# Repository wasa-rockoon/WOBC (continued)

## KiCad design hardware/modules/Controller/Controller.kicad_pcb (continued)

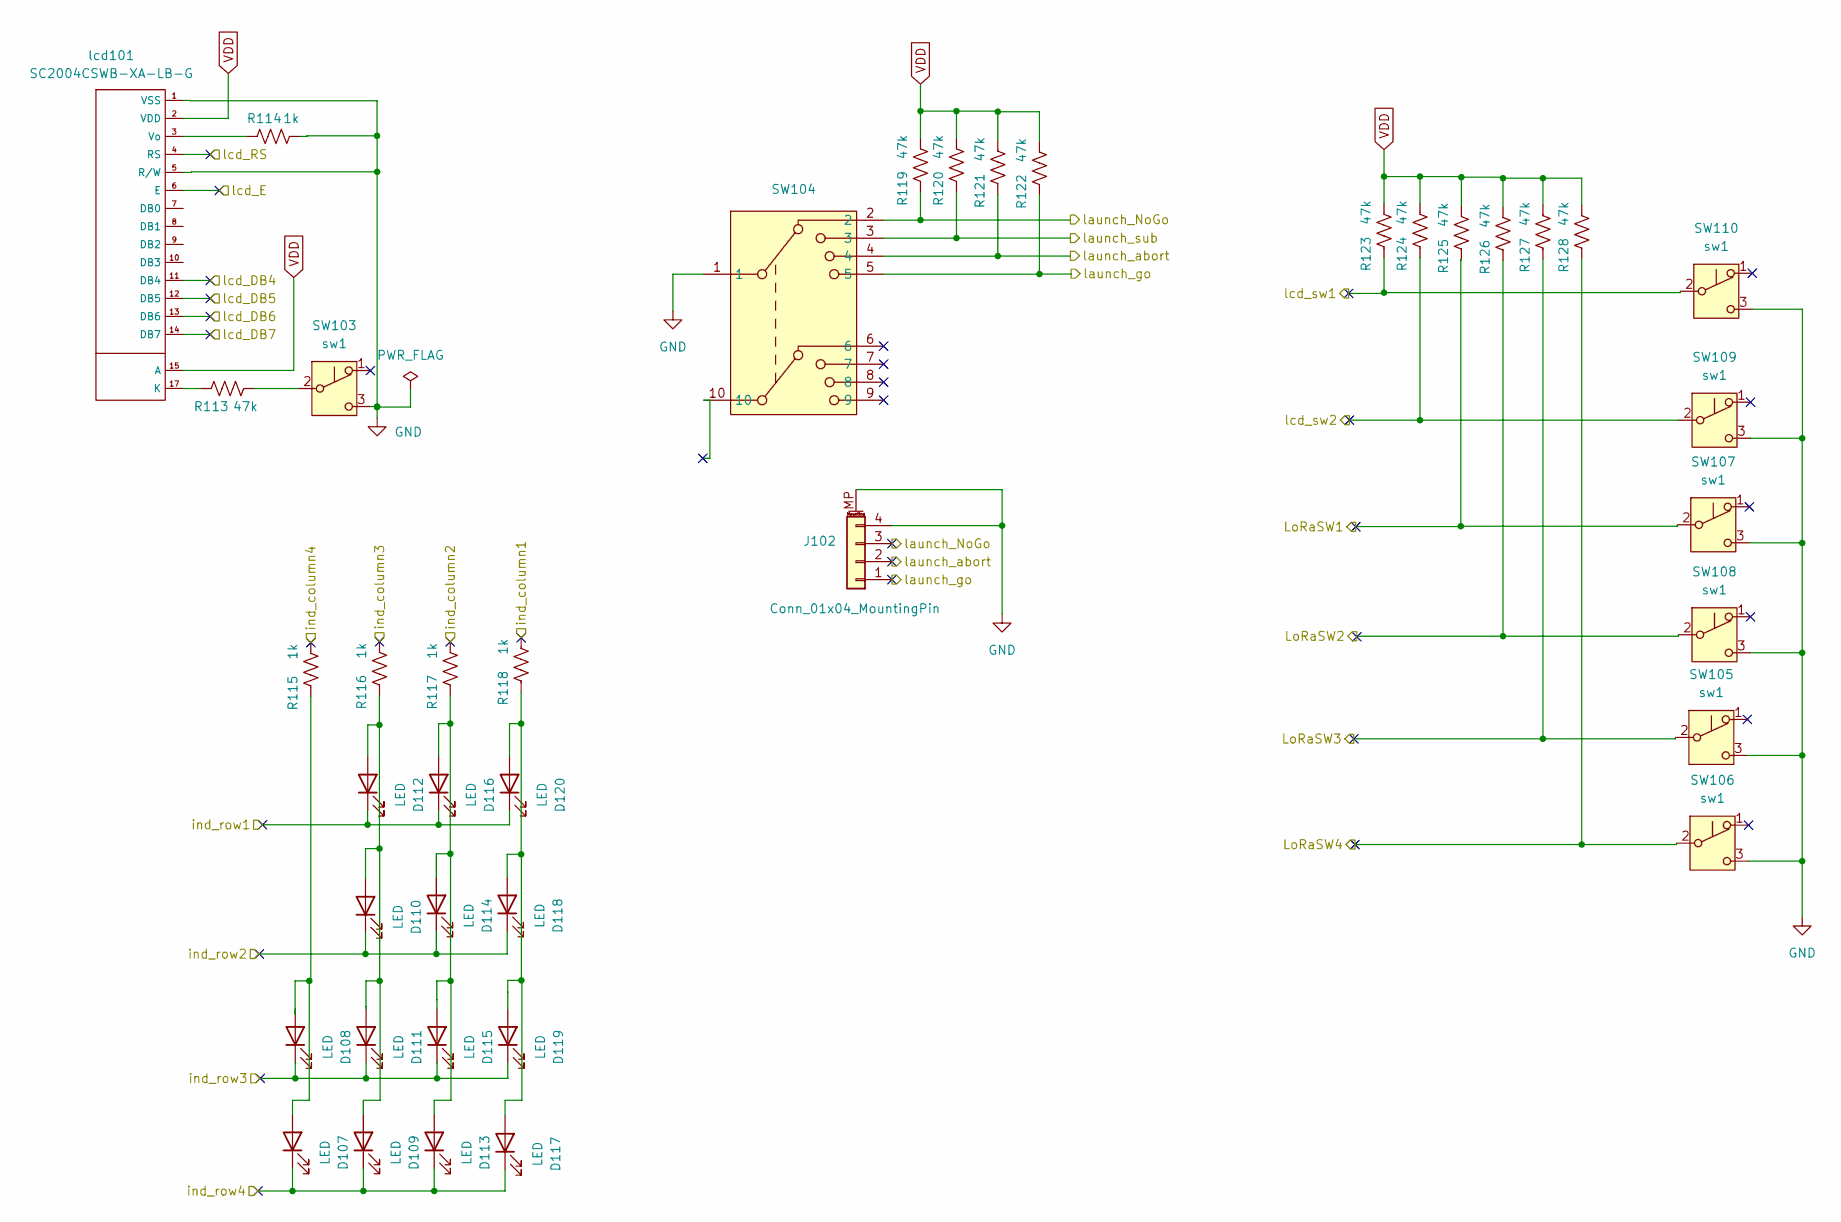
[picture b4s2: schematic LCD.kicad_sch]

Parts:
D107, D108, D109, D110, D111, D112, D113, D114, D115, D116, D117, D118, D119, D120: LED; LED_D3.0mm_FlatTop
J102: Conn_01x04_MountingPin; Grove_4P_L_SMD
R113, R119, R120, R121, R122, R123, R124, R125, R126, R127, R128: 47k; C_0402_1005Metric; LCSC C25792
R114, R115, R116, R117, R118: 1k; C_0402_1005Metric; LCSC C11702
SW103, SW105, SW106, SW107, SW108, SW109, SW110: sw1; ToggleSwitch
SW104: RotarySwitch_2x04
lcd101: SC2004CSWB-XA-LB-G; SC2004CSWB

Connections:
/DB4: lcd101.11 (DB4); also elsewhere on the board
/DB5: lcd101.12 (DB5); also elsewhere on the board
/DB6: lcd101.13 (DB6); also elsewhere on the board
/DB7: lcd101.14 (DB7); also elsewhere on the board
/E: lcd101.6 (E); also elsewhere on the board
/Go: J102.1, R122.2, SW104.5; also elsewhere on the board
/LoRa1sw: R125.2, SW107.2 (B); also elsewhere on the board
/LoRa2sw: R126.2, SW108.2 (B); also elsewhere on the board
/LoRa3sw: R127.2, SW105.2 (B); also elsewhere on the board
/LoRa4sw: R128.2, SW106.2 (B); also elsewhere on the board
/NoGo: J102.3, R119.2, SW104.2; also elsewhere on the board
/RS: lcd101.4 (RS); also elsewhere on the board
/abort: J102.2, R121.2, SW104.4; also elsewhere on the board
/col1: R118.1; also elsewhere on the board
/col2: R117.1; also elsewhere on the board
/col3: R116.1; also elsewhere on the board
/col4: R115.1; also elsewhere on the board
/lcd_sw1: R123.2, SW110.2 (B); also elsewhere on the board
/lcd_sw2: R124.2, SW109.2 (B); also elsewhere on the board
/raw1: D112.1 (K), D116.1 (K), D120.1 (K); also elsewhere on the board
/raw2: D110.1 (K), D114.1 (K), D118.1 (K); also elsewhere on the board
/raw3: D108.1 (K), D111.1 (K), D115.1 (K), D119.1 (K); also elsewhere on the board
/raw4: D107.1 (K), D109.1 (K), D113.1 (K), D117.1 (K); also elsewhere on the board
/sub: R120.2, SW104.3; also elsewhere on the board
GND: J102.4, J102.MP (MountPin), R114.1, SW103.3 (C), SW104.1, SW105.3 (C), SW106.3 (C), SW107.3 (C), SW108.3 (C), SW109.3 (C), SW110.3 (C), lcd101.1 (VSS), lcd101.5 (R/W); also elsewhere on the board
unnamed: D107.2 (A), D108.2 (A), R115.2
unnamed: D109.2 (A), D110.2 (A), D111.2 (A), D112.2 (A), R116.2
unnamed: D113.2 (A), D114.2 (A), D115.2 (A), D116.2 (A), R117.2
unnamed: D117.2 (A), D118.2 (A), D119.2 (A), D120.2 (A), R118.2
unnamed: R113.1, SW103.2 (B)
unnamed: R113.2, lcd101.17 (K)
unnamed: R114.2, lcd101.3 (Vo)
VDD: R119.1, R120.1, R121.1, R122.1, R123.1, R124.1, R125.1, R126.1, R127.1, R128.1, lcd101.2 (VDD), lcd101.15 (A); also elsewhere on the board

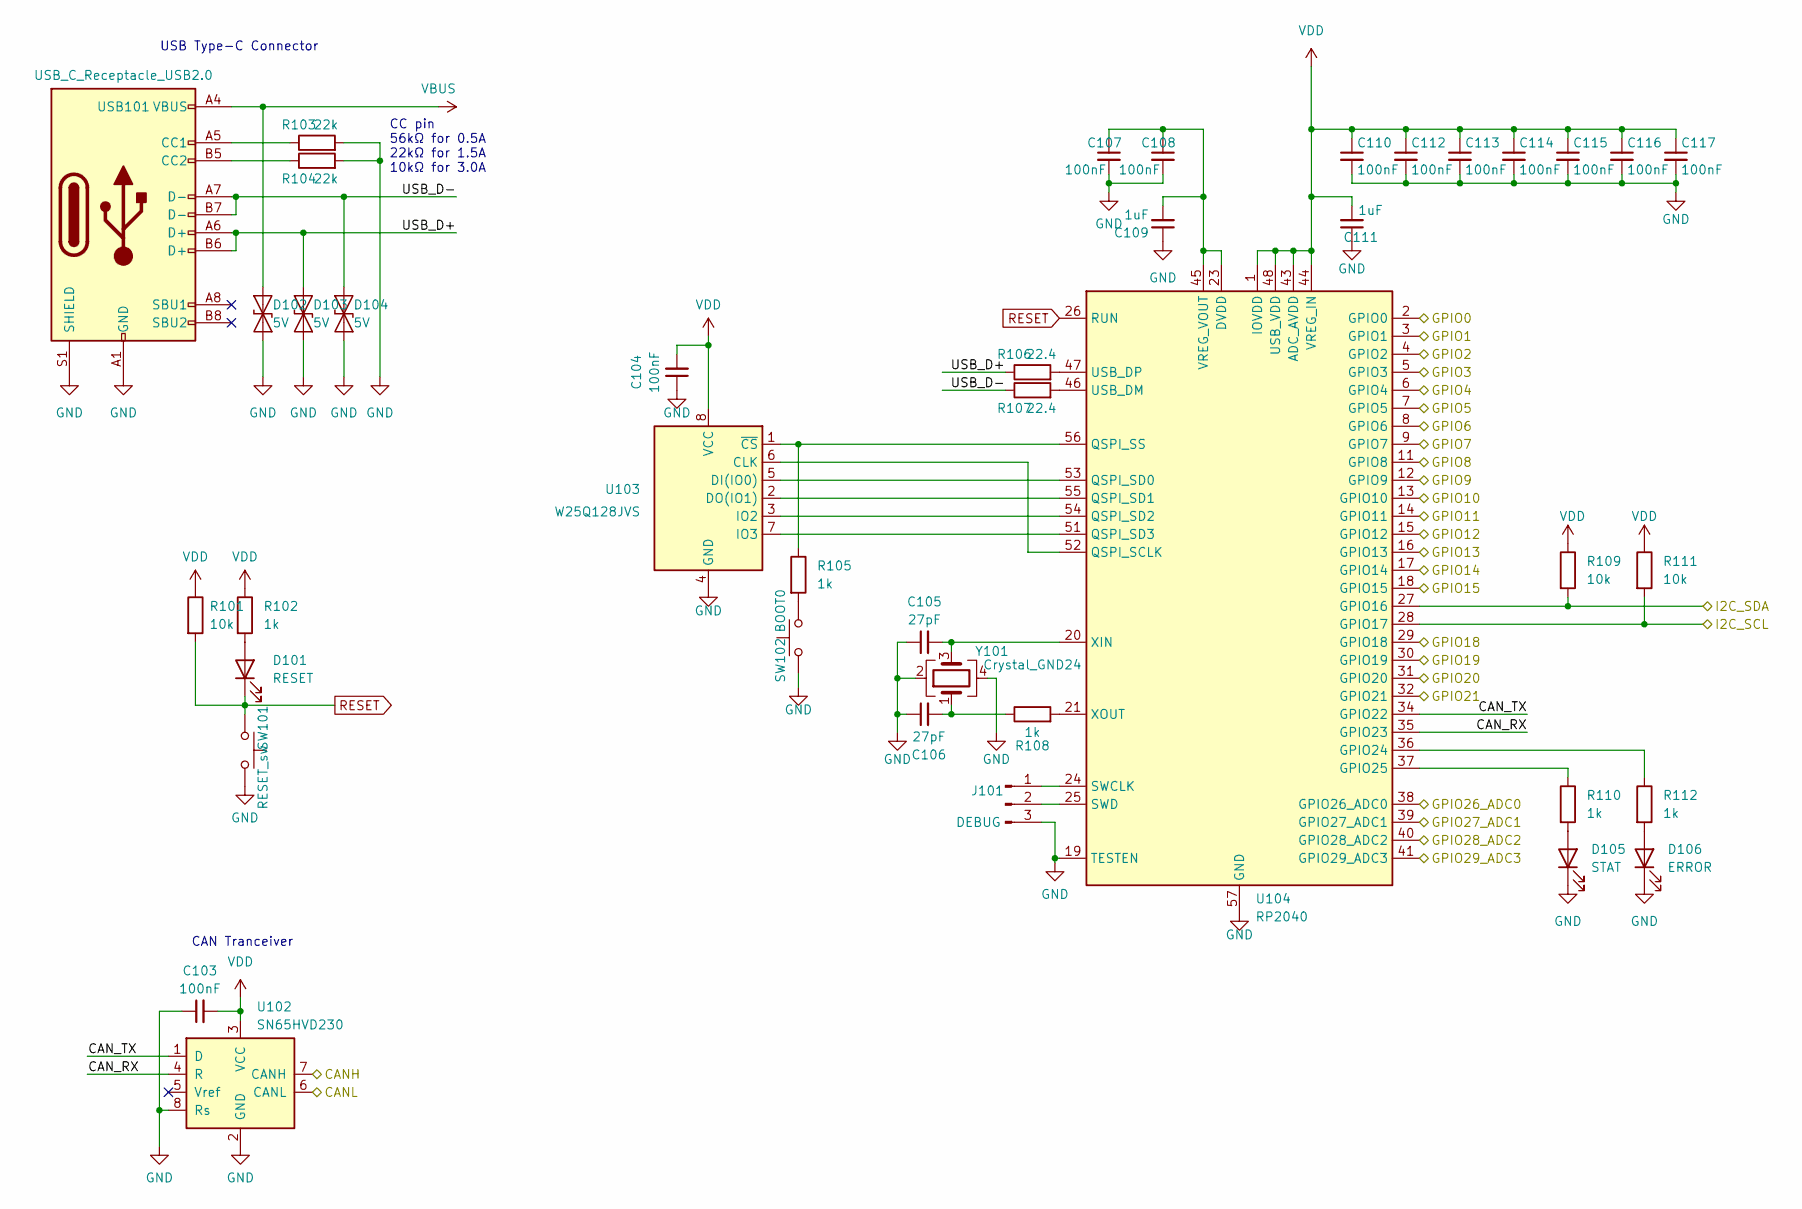
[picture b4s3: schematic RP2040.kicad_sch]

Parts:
C103, C104, C107, C108, C110, C112, C113, C114, C115, C116, C117: 100nF; C_0402_1005Metric; LCSC C1525
C105, C106: 27pF; C_0402_1005Metric; LCSC C1555
C109, C111: 1uF; C_0402_1005Metric; LCSC C52923
D101: RESET; LED_0805_2012Metric; LCSC C2296
D102, D103, D104: 5V; D_SOD-882; LCSC C7420372
D105: STAT; LED_0805_2012Metric; LCSC C2297
D106: ERROR; LED_0805_2012Metric; LCSC C84256
J101: DEBUG; PinHeader_1x03_P1.27mm_Vertical
R101, R109, R111: 10k; R_0402_1005Metric; LCSC C25744
R102, R105, R108, R110, R112: 1k; R_0402_1005Metric; LCSC C11702
R103, R104: 22k; R_0402_1005Metric; LCSC C25768
R106, R107: 22.4; R_0402_1005Metric; LCSC C25092
SW101: RESET_sw; TVAF06-A020B-R
SW102: BOOT0; TVAF06-A020B-R
U102: SN65HVD230; SOIC-8_3.9x4.9mm_P1.27mm; LCSC C12084
U103: W25Q128JVS; SOIC-8_5.23x5.23mm_P1.27mm; LCSC C97521
U104: RP2040; QFN-56-1EP_7x7mm_P0.4mm_EP3.2x3.2mm; LCSC C2040
USB101: USB_C_Receptacle_USB2.0; USB_C_TYPEC-301S-ACP16X7; LCSC C2856766
Y101: Crystal_GND24; Crystal_SMD_3225-4Pin_3.2x2.5mm; LCSC C9002

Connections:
/DB4: U104.11 (GPIO8); also elsewhere on the board
/DB5: U104.12 (GPIO9); also elsewhere on the board
/DB6: U104.13 (GPIO10); also elsewhere on the board
/DB7: U104.14 (GPIO11); also elsewhere on the board
/E: U104.9 (GPIO7); also elsewhere on the board
/Go: U104.5 (GPIO3); also elsewhere on the board
/LoRa1sw: U104.18 (GPIO15); also elsewhere on the board
/LoRa2sw: U104.17 (GPIO14); also elsewhere on the board
/LoRa3sw: U104.16 (GPIO13); also elsewhere on the board
/LoRa4sw: U104.15 (GPIO12); also elsewhere on the board
/ModuleIF/CANH: U102.7 (CANH); also elsewhere on the board
/ModuleIF/CANL: U102.6 (CANL); also elsewhere on the board
/NoGo: U104.2 (GPIO0); also elsewhere on the board
/RP2040/CAN_RX: U102.4 (R), U104.35 (GPIO23)
/RP2040/CAN_TX: U102.1 (D), U104.34 (GPIO22)
/RP2040/I2C_SCL: R111.2, U104.28 (GPIO17)
/RP2040/I2C_SDA: R109.2, U104.27 (GPIO16)
/RP2040/USB_D+: D103.2 (A2), R106.1, USB101.A6 (D+), USB101.B6 (D+)
/RP2040/USB_D-: D104.2 (A2), R107.1, USB101.A7 (D-), USB101.B7 (D-)
/RS: U104.6 (GPIO4); also elsewhere on the board
/abort: U104.4 (GPIO2); also elsewhere on the board
/col1: U104.38 (GPIO26_ADC0); also elsewhere on the board
/col2: U104.39 (GPIO27_ADC1); also elsewhere on the board
/col3: U104.40 (GPIO28_ADC2); also elsewhere on the board
/col4: U104.41 (GPIO29_ADC3); also elsewhere on the board
/lcd_sw1: U104.32 (GPIO21); also elsewhere on the board
/lcd_sw2: U104.31 (GPIO20); also elsewhere on the board
/raw1: U104.7 (GPIO5); also elsewhere on the board
/raw2: U104.8 (GPIO6); also elsewhere on the board
/raw3: U104.29 (GPIO18); also elsewhere on the board
/raw4: U104.30 (GPIO19); also elsewhere on the board
/sub: U104.3 (GPIO1); also elsewhere on the board
GND: C103.1, C104.1, C105.1, C106.1, C107.2, C108.2, C109.1, C110.2, C111.1, C112.2, C113.2, C114.2, C115.2, C116.2, C117.2, D102.1 (A1), D103.1 (A1), D104.1 (A1), D105.1 (K), D106.1 (K), J101.3, R103.2, R104.2, SW101.2, SW102.1, U102.2 (GND), U102.8 (Rs), U103.4 (GND), U104.19 (TESTEN), U104.57 (GND), USB101.A1 (GND), USB101.A12 (GND), USB101.B1 (GND), USB101.B12 (GND), USB101.S1 (SHIELD), Y101.2, Y101.4; also elsewhere on the board
unnamed: C106.2, R108.1, Y101.1
unnamed: D101.2 (A), R102.2
unnamed: D105.2 (A), R110.2
unnamed: D106.2 (A), R112.2
unnamed: J101.1, U104.24 (SWCLK)
unnamed: J101.2, U104.25 (SWD)
unnamed: R105.2, SW102.2
unnamed: U103.6 (CLK), U104.52 (QSPI_SCLK)
unnamed: U103.5 (DI(IO0)), U104.53 (QSPI_SD0)
unnamed: U103.2 (DO(IO1)), U104.55 (QSPI_SD1)
unnamed: U103.3 (IO2), U104.54 (QSPI_SD2)
unnamed: U103.7 (IO3), U104.51 (QSPI_SD3)
unnamed: R105.1, U103.1 (~CS), U104.56 (QSPI_SS)
unnamed: R112.1, U104.36 (GPIO24)
unnamed: R110.1, U104.37 (GPIO25)
unnamed: R107.2, U104.46 (USB_DM)
unnamed: R106.2, U104.47 (USB_DP)
unnamed: C107.1, C108.1, C109.2, U104.23 (DVDD), U104.45 (VREG_VOUT), U104.50 (DVDD)
unnamed: C105.2, U104.20 (XIN), Y101.3
unnamed: R108.2, U104.21 (XOUT)
unnamed: R103.1, USB101.A5 (CC1)
unnamed: R104.1, USB101.B5 (CC2)
RESET: D101.1 (K), R101.2, SW101.1, U104.26 (RUN)
VBUS: D102.2 (A2), USB101.A4 (VBUS), USB101.A9 (VBUS), USB101.B4 (VBUS), USB101.B9 (VBUS); also elsewhere on the board
VDD: C103.2, C104.2, C110.1, C111.2, C112.1, C113.1, C114.1, C115.1, C116.1, C117.1, R101.1, R102.1, R109.1, R111.1, U102.3 (VCC), U103.8 (VCC), U104.1 (IOVDD), U104.10 (IOVDD), U104.22 (IOVDD), U104.33 (IOVDD), U104.42 (IOVDD), U104.43 (ADC_AVDD), U104.44 (VREG_IN), U104.48 (USB_VDD), U104.49 (IOVDD); also elsewhere on the board

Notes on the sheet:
CAN Tranceiver
USB Type-C Connector
CC pin 56kΩ for 0.5A 22kΩ for 1.5A 10kΩ for 3.0A

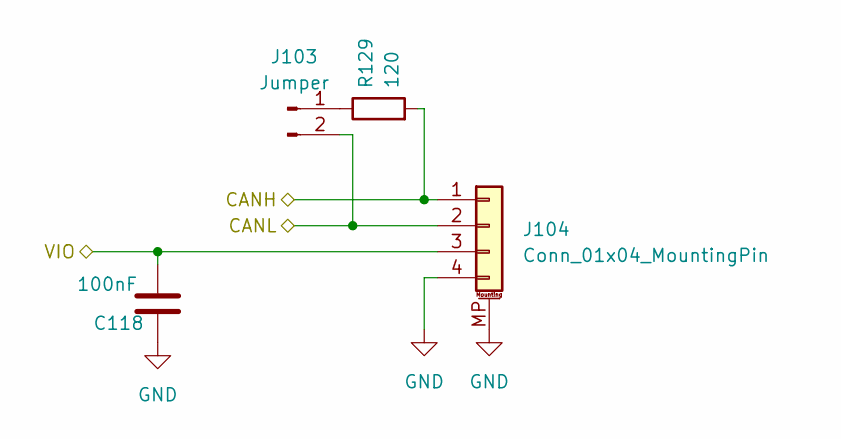
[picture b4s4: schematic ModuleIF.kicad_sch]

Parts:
C118: 100nF; C_0402_1005Metric; LCSC C1525
J103: Jumper; PinHeader_1x02_P1.27mm_Vertical
J104: Conn_01x04_MountingPin; Grove_4P_L_SMD
R129: 120; R_0402_1005Metric; LCSC C25079

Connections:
/ModuleIF/CANH: J104.1, R129.2; also elsewhere on the board
/ModuleIF/CANL: J103.2, J104.2; also elsewhere on the board
GND: C118.1, J104.4, J104.MP (MountPin); also elsewhere on the board
unnamed: J103.1, R129.1
VDD: C118.2, J104.3; also elsewhere on the board

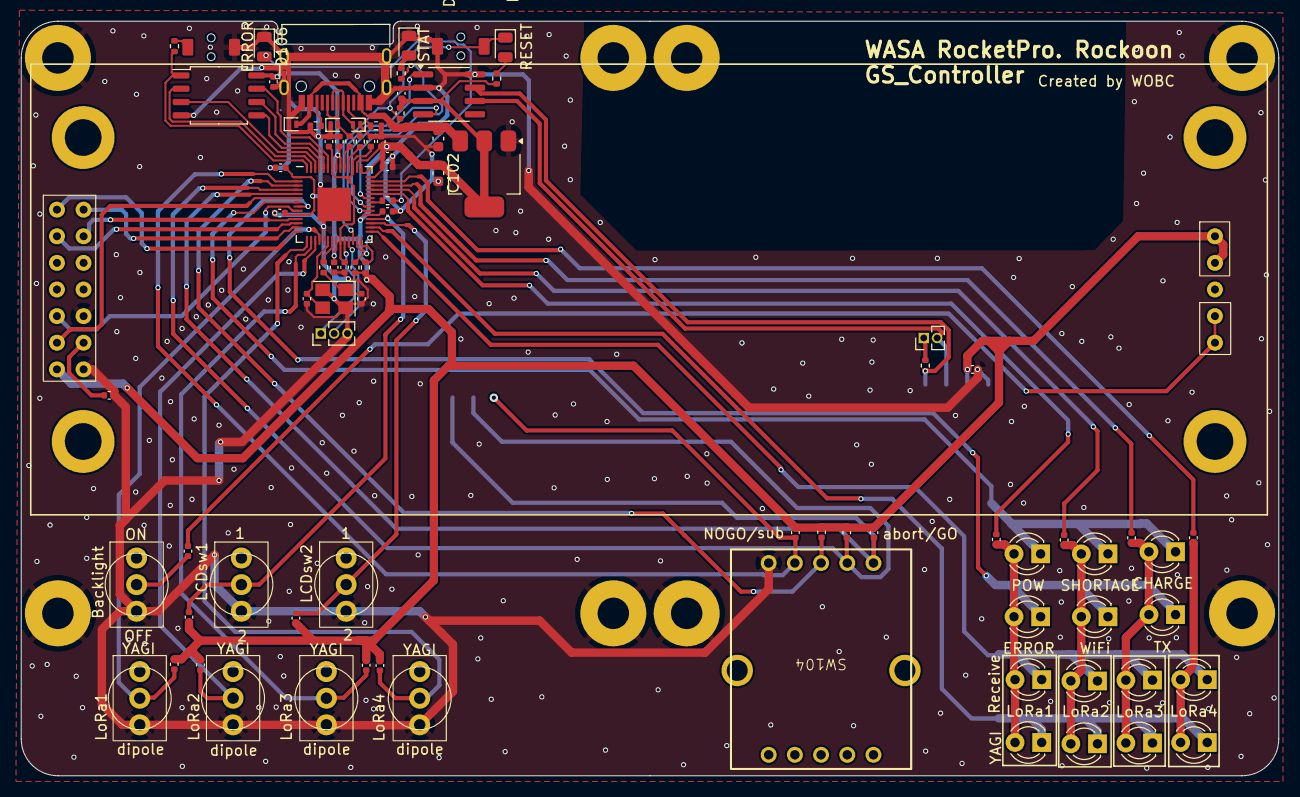
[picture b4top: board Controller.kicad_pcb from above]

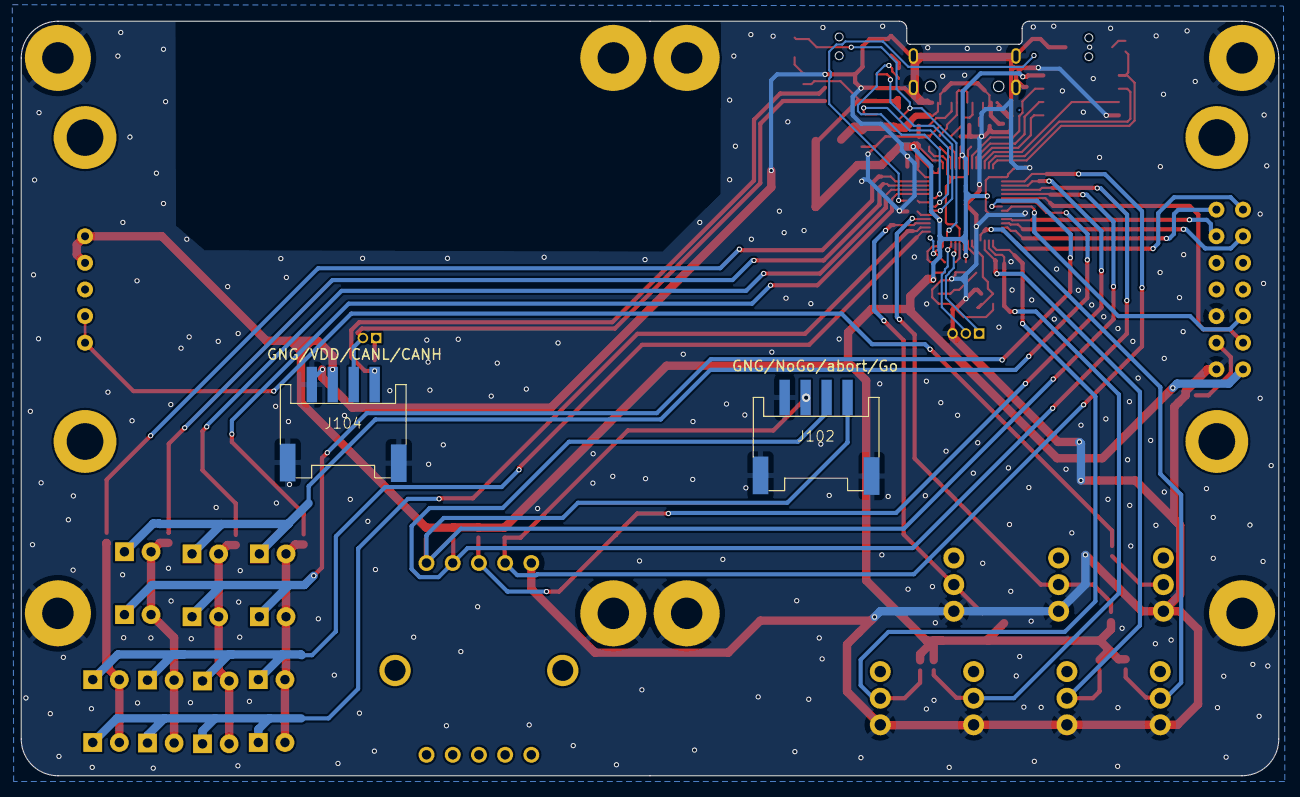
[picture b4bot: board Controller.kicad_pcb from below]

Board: 2 copper layers, 120.0 x 72.0 mm, 88 parts (2 on the bottom side), 66 nets.

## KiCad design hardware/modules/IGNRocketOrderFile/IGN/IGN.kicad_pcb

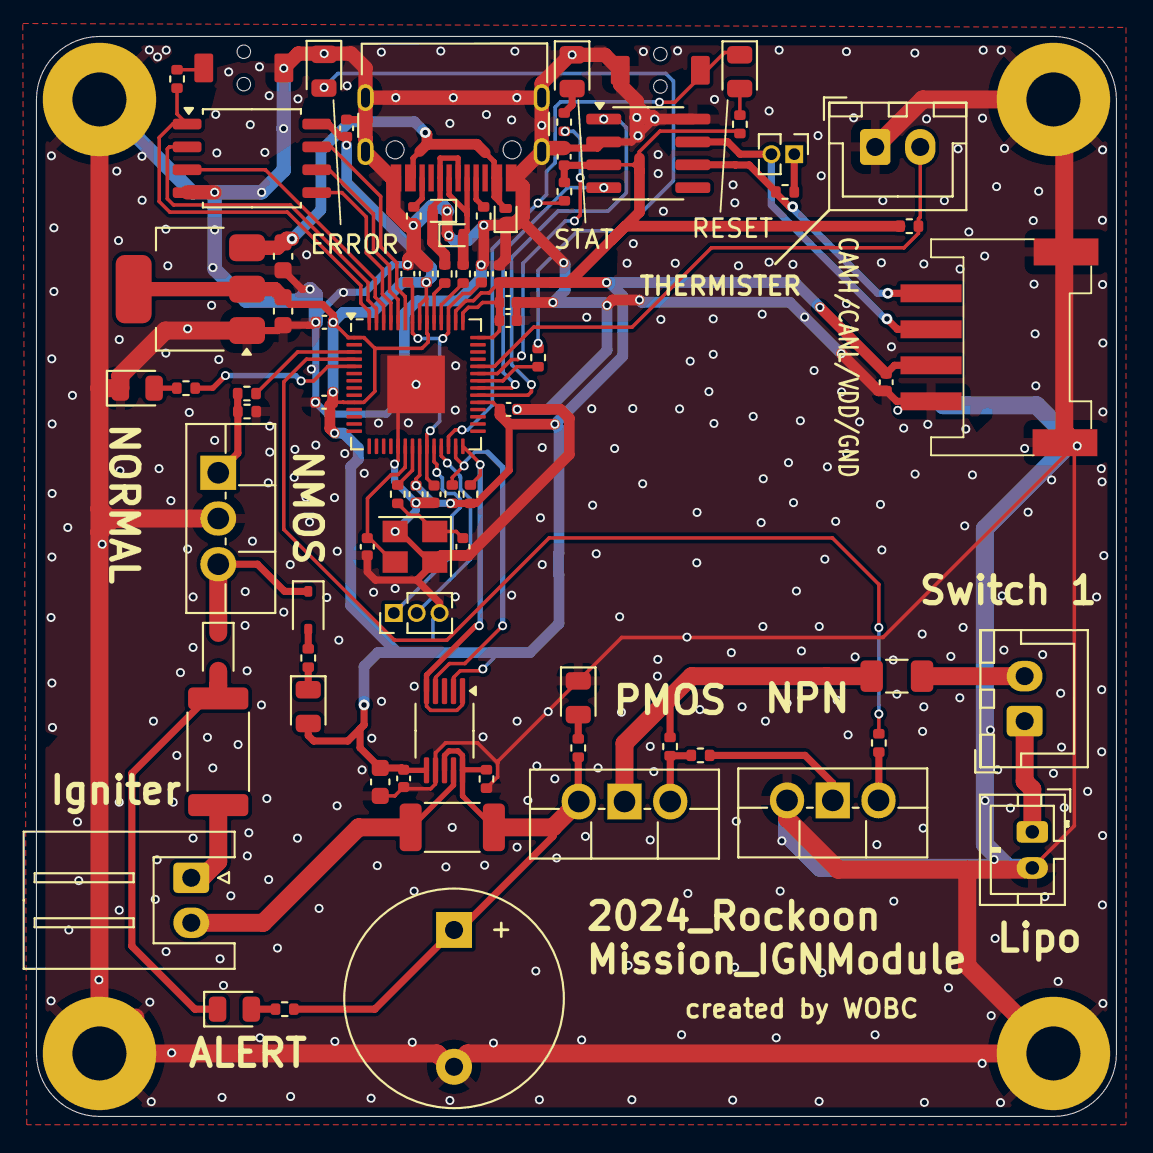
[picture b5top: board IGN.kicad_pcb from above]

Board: 2 copper layers, 60.0 x 60.0 mm, 79 parts (0 on the bottom side), 56 nets.

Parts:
BZ201: Buzzer; Buzzer_12x9.5RM7.6
C101, C102, C201: 10uF; C_0603_1608Metric
C202, C301, C302, C305, C306, C308, C310, C311, C312, C313, C314, C315, C401: 100nF; C_0402_1005Metric
C303, C304: 27pF; C_0402_1005Metric
C307, C309: 1uF; C_0402_1005Metric
D201: PMOS; LED_0805_2012Metric
D202, D204: D_Schottky; D_SOD-323
D203: ALERT; LED_0805_2012Metric
D205: NMOS; LED_0805_2012Metric
D206: NORMAL; LED_0805_2012Metric
D301: RESET; LED_0805_2012Metric
D302, D303, D304: 5V; D_SOD-882D
D305: STAT; LED_0805_2012Metric
D306: ERROR; LED_0805_2012Metric
F201: Polyfuse; Fuse_1206_3216Metric
J101: THERMISTER; JST_XH_B2B-XH-A_1x02_P2.50mm_Vertical
J201: IGNITER; JST_XH_S2B-XH-A_1x02_P2.50mm_Horizontal
J202: PowerSW; JST_XH_B2B-XH-A_1x02_P2.50mm_Vertical
J203: LiPo 1 Cell; JST_PH_B2B-PH-K_1x02_P2.00mm_Vertical
J301: DEBUG; PinHeader_1x03_P1.27mm_Vertical
J401: Jumper; PinHeader_1x02_P1.27mm_Vertical
J402: Conn_01x04_MountingPin; Grove_4P_L_SMD
Q201: Q_PMOS_GSD; TO-220F-3_Vertical
Q202: Q_NMOS_GSD; TO-220F-3_Vertical
Q203: Q_NPN_BEC; TO-220F-3_Vertical
R101, R202, R205, R206, R301, R309, R311: 10k; R_0402_1005Metric
R201, R208, R210, R211, R212, R302, R305, R308, R310, R312: 1k; R_0402_1005Metric
R203: 20mΩ; R_2010_5025Metric
R204: 1; R_2512_6332Metric
R207, R209: 510; R_0402_1005Metric
R303, R304: 5.1k; R_0402_1005Metric
R306, R307: 22.4; R_0402_1005Metric
R401: 120; R_0402_1005Metric
SW301: RESET_sw; TVAF06-A020B-R
SW302: BOOT0; TVAF06-A020B-R
U101: AMS1117-3.3; SOT-223-3_TabPin2
U201: INA226; VSSOP-10_3x3mm_P0.5mm
U301: SN65HVD230; SOIC-8_3.9x4.9mm_P1.27mm
U302: W25Q128JVS; SOIC-8_5.23x5.23mm_P1.27mm
U303: RP2040; QFN-56-1EP_7x7mm_P0.4mm_EP3.2x3.2mm
USB301: USB_C_Receptacle_USB2.0; USB_C_TYPEC-301S-ACP16X7
Y301: Crystal_GND24; Crystal_SMD_3225-4Pin_3.2x2.5mm

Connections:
/HIGH: R211.1, U303.4 (GPIO2)
/I2C_SCL: R311.2, U201.1 (A1), U201.5 (SCL), U303.28 (GPIO17)
/I2C_SDA: R309.2, U201.4 (SDA), U303.27 (GPIO16)
/IF/CANH: J402.1, R401.2, U301.6 (CANL)
/IF/CANL: J401.2, J402.2, U301.7 (CANH)
/LOW: R209.1, U303.3 (GPIO1)
/Normal: R212.1, U303.5 (GPIO3)
/RP2040core/CAN_RX: U301.4 (R), U303.35 (GPIO23)
/RP2040core/CAN_TX: U301.1 (D), U303.34 (GPIO22)
/RP2040core/GPIO26_ADC0: J101.2, R101.2, U303.38 (GPIO26_ADC0)
/RP2040core/USB_D+: D303.2 (A2), R306.1, USB301.A6 (D+), USB301.B6 (D+)
/RP2040core/USB_D-: D304.2 (A2), R307.1, USB301.A7 (D-), USB301.B7 (D-)
GND: BZ201.2 (-), C101.2, C102.2, C201.2, C202.2, C301.1, C302.1, C303.1, C304.1, C305.2, C306.2, C307.1, C308.2, C309.1, C310.2, C311.2, C312.2, C313.2, C314.2, C315.2, C401.1, D201.1 (K), D206.1 (K), D302.1 (A1), D303.1 (A1), D304.1 (A1), D305.1 (K), D306.1 (K), J101.1, J203.2, J301.3, J402.4, J402.MP (MountPin), Q202.3 (D), Q203.3 (E), R202.1, R206.1, R303.2, R304.2, SW301.2, SW302.1, U101.1 (GND), U201.7 (GND), U301.2 (GND), U301.8 (Rs), U302.4 (GND), U303.19 (TESTEN), U303.57 (GND), USB301.A1 (GND), USB301.A12 (GND), USB301.B1 (GND), USB301.B12 (GND), USB301.S1 (SHIELD), Y301.2, Y301.4
unnamed: BZ201.1 (+), Q201.3 (S), R201.1, R202.2, R203.2, R208.1, U201.8 (Vbus), U201.10 (Vin+)
unnamed: C304.2, R308.1, Y301.1
unnamed: D201.2 (A), R201.2
unnamed: D202.2 (A), D203.1 (K), R204.2
unnamed: D202.1 (K), D204.1 (K), Q202.2 (S)
unnamed: D203.2 (A), R208.2
unnamed: D204.2 (A), R210.2
unnamed: D205.1 (K), R210.1
unnamed: D206.2 (A), R212.2
unnamed: D301.2 (A), R302.2
unnamed: D305.2 (A), R310.2
unnamed: D306.2 (A), R312.2
unnamed: J201.1, R204.1
unnamed: J201.2, R203.1, U201.9 (Vin-)
unnamed: J202.1, J203.1
unnamed: F201.1, J202.2
unnamed: J301.1, U303.24 (SWCLK)
unnamed: J301.2, U303.25 (SWD)
unnamed: J401.1, R401.1
unnamed: F201.2, Q201.1 (D), R205.1
unnamed: Q201.2 (G), R205.2, R207.1
unnamed: Q202.1 (G), R206.2, R209.2
unnamed: Q203.2 (B), R211.2
unnamed: Q203.1 (C), R207.2
unnamed: R305.2, SW302.2
unnamed: U302.6 (CLK), U303.52 (QSPI_SCLK)
unnamed: U302.5 (DI(IO0)), U303.53 (QSPI_SD0)
unnamed: U302.2 (DO(IO1)), U303.55 (QSPI_SD1)
unnamed: U302.3 (IO2), U303.54 (QSPI_SD2)
unnamed: U302.7 (IO3), U303.51 (QSPI_SD3)
unnamed: R305.1, U302.1 (~CS), U303.56 (QSPI_SS)
unnamed: R312.1, U303.36 (GPIO24)
unnamed: R310.1, U303.37 (GPIO25)
unnamed: R307.2, U303.46 (USB_DM)
unnamed: R306.2, U303.47 (USB_DP)
unnamed: C305.1, C306.1, C307.2, U303.23 (DVDD), U303.45 (VREG_VOUT), U303.50 (DVDD)
unnamed: C303.2, U303.20 (XIN), Y301.3
unnamed: R308.2, U303.21 (XOUT)
unnamed: R303.1, USB301.A5 (CC1)
unnamed: R304.1, USB301.B5 (CC2)
RESET: D301.1 (K), R301.2, SW301.1, U303.26 (RUN)
VBUS: C101.1, D302.2 (A2), U101.3 (VI), USB301.A4 (VBUS), USB301.A9 (VBUS), USB301.B4 (VBUS), USB301.B9 (VBUS)
VDD: C102.1, C201.1, C202.1, C301.2, C302.2, C308.1, C309.2, C310.1, C311.1, C312.1, C313.1, C314.1, C315.1, C401.2, D205.2 (A), J402.3, R101.1, R301.1, R302.1, R309.1, R311.1, U101.2 (VO), U201.2 (A0), U201.6 (VS), U301.3 (VCC), U302.8 (VCC), U303.1 (IOVDD), U303.10 (IOVDD), U303.22 (IOVDD), U303.33 (IOVDD), U303.42 (IOVDD), U303.43 (ADC_AVDD), U303.44 (VREG_IN), U303.48 (USB_VDD), U303.49 (IOVDD)
